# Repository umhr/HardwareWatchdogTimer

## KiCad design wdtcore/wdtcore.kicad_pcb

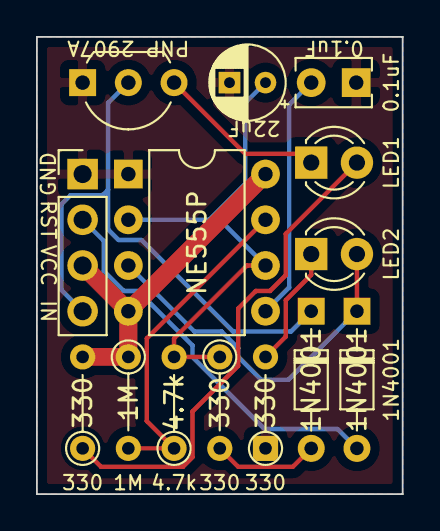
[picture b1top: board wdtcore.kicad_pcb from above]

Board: 2 copper layers, 20.3 x 25.4 mm, 14 parts (0 on the bottom side), 12 nets.

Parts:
0.1uF: 0.1uF; C_Rect_L4.0mm_W2.5mm_P2.50mm
1M: 1M; R_Axial_DIN0204_L3.6mm_D1.6mm_P5.08mm_Vertical
1N4001, 1N4001#2: 1N4001; D_DO-34_SOD68_P7.62mm_Horizontal
4.7k: 4.7k; R_Axial_DIN0204_L3.6mm_D1.6mm_P5.08mm_Vertical
22uF: 22uF; CP_Radial_D4.0mm_P2.00mm
330, 330#2, 330#3: 330; R_Axial_DIN0204_L3.6mm_D1.6mm_P5.08mm_Vertical
GND: WDTcore; PinHeader_1x04_P2.54mm_Vertical
LED1, LED2: LED; LED_D3.0mm_Clear
NE555P: WDTcore; DIP-8_W7.62mm
PNP 2907A: Q_PNP_EBC; TO-92L_Inline_Wide

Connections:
GND: 0.1uF.2, 22uF.2, 330#3.1, GND.1, NE555P.1, PNP 2907A.3
unnamed: 4.7k.2, 22uF.1, 330#2.1, NE555P.2, NE555P.6
unnamed: 0.1uF.1, NE555P.5
unnamed: LED1.1, PNP 2907A.1
unnamed: 330.1, LED1.2
unnamed: 330#3.2, LED2.1
unnamed: 1N4001.1, LED2.2, NE555P.3
unnamed: 1N4001#2.1, GND.4, PNP 2907A.2
unnamed: 1N4001#2.2, 330#2.2
unnamed: 1N4001.2, GND.2
unnamed: 1M.2, 4.7k.1, NE555P.7
VCC: 1M.1, 330.2, GND.3, NE555P.4, NE555P.8
